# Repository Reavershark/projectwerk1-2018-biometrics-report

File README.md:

# projectwerk1-2018-biometrics-report
Report document of the course "projectwerk 1"

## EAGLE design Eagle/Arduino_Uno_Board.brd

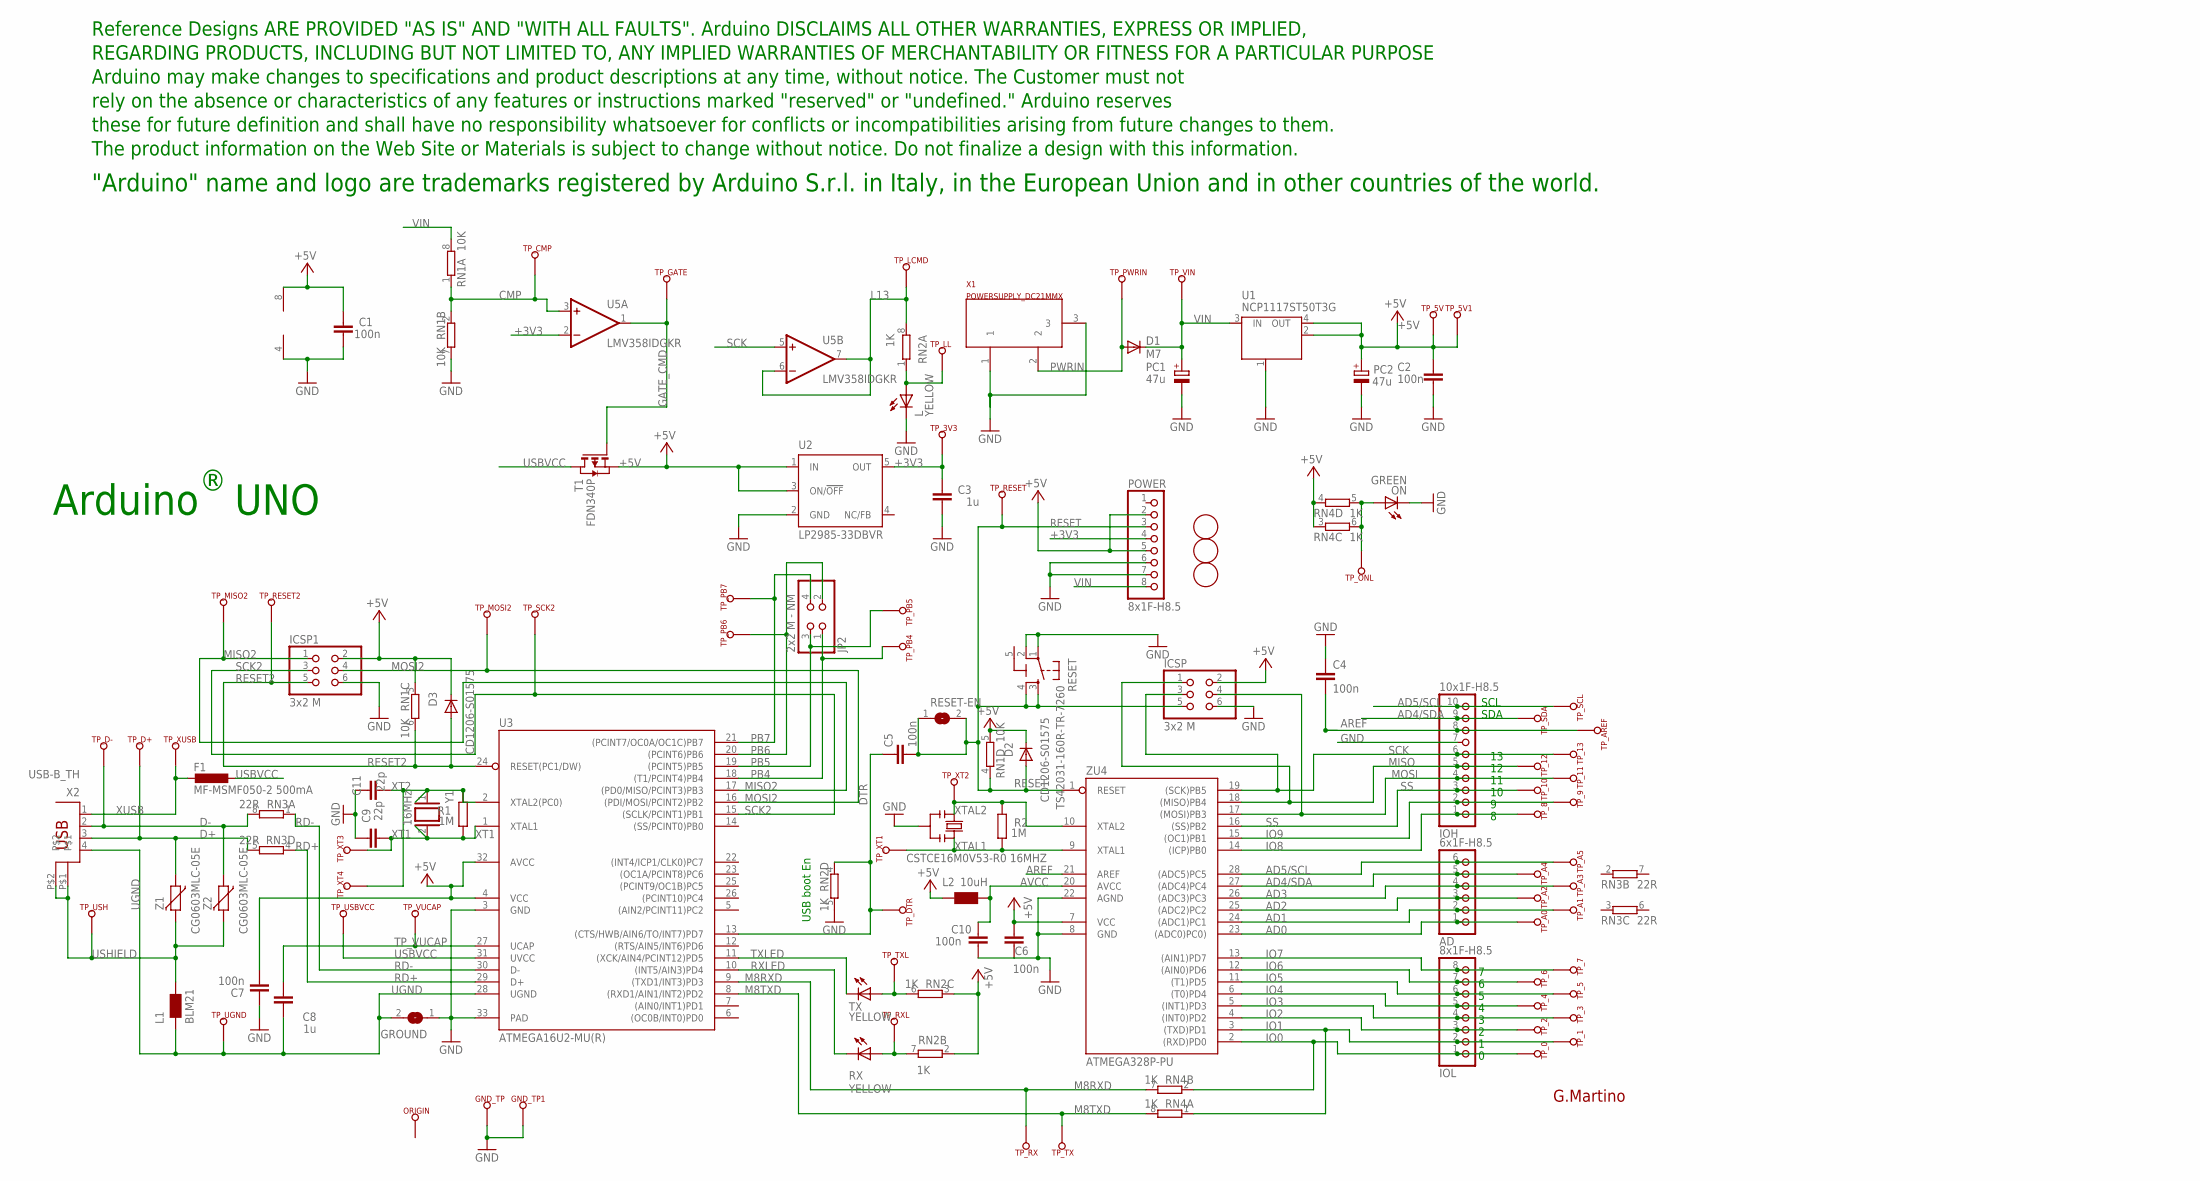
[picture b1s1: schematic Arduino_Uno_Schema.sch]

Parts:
AD: 6x1F-H8.5; 1X06
C1, C2, C4, C5, C6, C7, C10: 100n; C0603-ROUND
C3, C8: 1u; C0603-ROUND
C9, C11: 22p; C0603-ROUND
D1: M7; SMB
D2, D3: CD1206-S01575; MINIMELF
F1: MF-MSMF050-2 500mA; L1812
FD1, FD2, FD3: FIDUCIALMOUNT; FIDUCIA-MOUNT
GND_TP, GND_TP1: TP_SP; TP-SP
GROUND: SJ
ICSP, ICSP1: 3x2 M; 2X03
IOH: 10x1F-H8.5; 1X10
IOL: 8x1F-H8.5; 1X08
JP2: 2x2 M - NM; 2X02
L: YELLOW; CHIP-LED0805
L1: BLM21; 0805
L2: 10uH; 0805
ON: GREEN; CHIP-LED0805
ORIGIN: TP_SP; TP-SP
PC1, PC2: 47u; PANASONIC_D
POWER: 8x1F-H8.5; 1X08
R1, R2: 1M; R0603-ROUND
RESET: TS42031-160R-TR-7260; TS42
RESET-EN: SJ
RN1: 10K; CAY16
RN2, RN4: 1K; CAY16
RN3: 22R; CAY16
RX: YELLOW; CHIP-LED0805
T1: FDN340P; SOT-23
TP_0, TP_1, TP_2, TP_3, TP_3V3, TP_4, TP_5, TP_5V, TP_5V1, TP_6, TP_7, TP_8, TP_9, TP_10, TP_11, TP_12, TP_13: TP_SP; TP-SP
TP_A0, TP_A1, TP_A2, TP_A3, TP_A4, TP_A5: TP_SP; TP-SP
TP_AREF: TP_SP; TP-SP
TP_CMP: TP_SP; TP-SP
TP_D+: TP_SP; TP-SP
TP_D-: TP_SP; TP-SP
TP_DTR: TP_SP; TP-SP
TP_GATE: TP_SP; TP-SP
TP_LCMD: TP_SP; TP-SP
TP_LL: TP_SP; TP-SP
TP_MISO2: TP_SP; TP-SP
TP_MOSI2: TP_SP; TP-SP
TP_ONL: TP_SP; TP-SP
TP_PB4, TP_PB5, TP_PB6, TP_PB7: TP_SP; TP-SP
TP_PWRIN: TP_SP; TP-SP
TP_RESET, TP_RESET2: TP_SP; TP-SP
TP_RX: TP_SP; TP-SP
TP_RXL: TP_SP; TP-SP
TP_SCK2: TP_SP; TP-SP
TP_SCL: TP_SP; TP-SP
TP_SDA: TP_SP; TP-SP
TP_TX: TP_SP; TP-SP
TP_TXL: TP_SP; TP-SP
TP_UGND: TP_SP; TP-SP
TP_USBVCC: TP_SP; TP-SP
TP_USH: TP_SP; TP-SP
TP_VIN: TP_SP; TP-SP
TP_VUCAP: TP_SP; TP-SP
TP_XT1, TP_XT2, TP_XT3, TP_XT4: TP_SP; TP-SP
TP_XUSB: TP_SP; TP-SP
TX: YELLOW; CHIP-LED0805
U1: NCP1117ST50T3G; SOT223
U2: LP2985-33DBVR; SOT23-DBV
U3: ATMEGA16U2-MU(R); MLF32
U5: LMV358IDGKR; MSOP08
U$1: DISCLAIMER
X1: POWERSUPPLY_DC21MMX; POWERSUPPLY_DC-21MM
X2: USB-B_TH; PN61729
Y1: 16MHz; QS
Y2: CSTCE16M0V53-R0 16MHZ; RESONATOR
Z1, Z2: CG0603MLC-05E; CT/CN0603
ZU4: ATMEGA328P-PU; DIL28-3

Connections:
5-GND: RESET.5 (5-GND)
+3V3: C3.2, POWER.4, TP_3V3.X, U2.5 (OUT), U5.2 (-IN)
+5V: C1.2, C2.2, C6.2, C7.1, D2.C, D3.C, ICSP.2, ICSP1.2, L2.1, PC2.+, POWER.2, POWER.5, RN1.3 (1), RN1.5 (2), RN2.2 (1), RN2.3 (1), RN4.3 (1), RN4.4 (1), T1.2 (S), TP_5V.X, TP_5V1.X, U1.2 (OUT), U1.4 (OUT), U2.1 (IN), U2.3 (ON/!OFF), U3.4 (VCC), U3.32 (AVCC), U5.8 (V+), ZU4.7 (VCC)
AD0: AD.1, TP_A0.X, ZU4.23 ((ADC0)PC0))
AD1: AD.2, TP_A1.X, ZU4.24 ((ADC1)PC1)
AD2: AD.3, TP_A2.X, ZU4.25 ((ADC2)PC2)
AD3: AD.4, TP_A3.X, ZU4.26 ((ADC3)PC3)
AD4/SDA: AD.5, IOH.9, TP_A4.X, TP_SDA.X, ZU4.27 ((ADC4)PC4)
AD5/SCL: AD.6, IOH.10, TP_A5.X, TP_SCL.X, ZU4.28 ((ADC5)PC5)
AREF: C4.2, IOH.8, TP_AREF.X, ZU4.21 (AREF)
AVCC: C10.2, L2.2, ZU4.20 (AVCC)
CMP: RN1.1, RN1.2 (1), TP_CMP.X, U5.3 (+IN)
D+: RN3.5 (2), TP_D+.X, X2.3, Z1.1
D-: RN3.8 (2), TP_D-.X, X2.2, Z2.1
DTR: C5.1, RN2.4 (1), TP_DTR.X, U3.13 ((CTS/HWB/AIN6/TO/INT7)PD7)
GATE_CMD: T1.3 (G), TP_GATE.X, U5.1 (OUT)
GND: C1.1, C2.1, C3.1, C4.1, C6.1, C7.2, C9.2, C10.1, C11.2, GND_TP.X, GND_TP1.X, GROUND.1, ICSP.6, ICSP1.6, IOH.7, L.C, ON.C, PC1.-, PC2.-, POWER.6, POWER.7, RESET.1, RESET.2, RN1.7 (2), RN2.5 (2), U1.1 (GND/ADJ), U2.2 (GND), U3.3 (GND), U3.33 (PAD), U5.4 (V-), X1.1, X1.3, Y2.2, ZU4.8 (GND), ZU4.22 (AGND)
IO0: IOL.1, RN4.2 (1), TP_0.X, ZU4.2 ((RXD)PD0)
IO1: IOL.2, RN4.1, TP_1.X, ZU4.3 ((TXD)PD1)
IO2: IOL.3, TP_2.X, ZU4.4 ((INT0)PD2)
IO3: IOL.4, TP_3.X, ZU4.5 ((INT1)PD3)
IO4: IOL.5, TP_4.X, ZU4.6 ((T0)PD4)
IO5: IOL.6, TP_5.X, ZU4.11 ((T1)PD5)
IO6: IOL.7, TP_6.X, ZU4.12 ((AIN0)PD6)
IO7: IOL.8, TP_7.X, ZU4.13 ((AIN1)PD7)
IO8: IOH.1, TP_8.X, ZU4.14 ((ICP)PB0)
IO9: IOH.2, TP_9.X, ZU4.15 ((OC1)PB1)
L13: RN2.8 (2), TP_LCMD.X, U5.6 (-IN), U5.7 (OUT)
M8RXD: RN4.7 (2), TP_RX.X, U3.9 ((TXD1/INT3)PD3)
M8TXD: RN4.8 (2), TP_TX.X, U3.8 ((RXD1/AIN1/INT2)PD2)
MISO: ICSP.1, IOH.5, TP_12.X, ZU4.18 ((MISO)PB4)
MISO2: ICSP1.1, TP_MISO2.X, U3.17 ((PD0/MISO/PCINT3)PB3)
MOSI: ICSP.4, IOH.4, TP_11.X, ZU4.17 ((MOSI)PB3)
MOSI2: ICSP1.4, TP_MOSI2.X, U3.16 ((PDI/MOSI/PCINT2)PB2)
unnamed: L.A, RN2.1, TP_LL.X
unnamed: ON.A, RN4.5 (2), RN4.6 (2), TP_ONL.X
unnamed: RN2.7 (2), RX.A, TP_RXL.X
unnamed: RN2.6 (2), TP_TXL.X, TX.A
PB4: JP2.1, TP_PB4.X, U3.18 ((T1/PCINT4)PB4)
PB5: JP2.3, TP_PB5.X, U3.19 ((PCINT5)PB5)
PB6: JP2.2, TP_PB6.X, U3.20 ((PCINT6)PB6)
PB7: JP2.4, TP_PB7.X, U3.21 ((PCINT7/OC0A/OC1C)PB7)
PWRIN: D1.A, TP_PWRIN.X, X1.2
RD+: RN3.4 (1), U3.29 (D+)
RD-: RN3.1, U3.30 (D-)
RESET: C5.2, D2.A, ICSP.5, POWER.3, RESET.3, RESET.4, RESET-EN.1, RESET-EN.2, RN1.4 (1), TP_RESET.X, ZU4.1 (RESET)
RESET2: D3.A, ICSP1.5, RN1.6 (2), TP_RESET2.X, U3.24 (RESET(PC1/DW))
RXLED: RX.C, U3.10 ((INT5/AIN3)PD4)
SCK: ICSP.3, IOH.6, TP_13.X, U5.5 (+IN), ZU4.19 ((SCK)PB5)
SCK2: ICSP1.3, TP_SCK2.X, U3.15 ((SCLK/PCINT1)PB1)
SS: IOH.3, TP_10.X, ZU4.16 ((SS)PB2)
TP_VUCAP: C8.1, TP_VUCAP.X, U3.27 (UCAP)
TXLED: TX.C, U3.11 ((XCK/AIN4/PCINT12)PD5)
UGND: C8.2, GROUND.2, L1.1, TP_UGND.X, U3.28 (UGND), X2.4
USBVCC: F1.1, T1.1 (D), TP_USBVCC.X, U3.31 (UVCC)
USHIELD: L1.2, TP_USH.X, X2.P$1, X2.P$2, Z1.2, Z2.2
VIN: D1.C, PC1.+, POWER.8, RN1.8 (2), TP_VIN.X, U1.3 (IN)
XT1: C9.1, R1.1, TP_XT3.X, U3.1 (XTAL1), Y1.2
XT2: C11.1, R1.2, TP_XT4.X, U3.2 (XTAL2(PC0)), Y1.1
XTAL1: R2.1, TP_XT1.X, Y2.3, ZU4.9 (XTAL1)
XTAL2: R2.2, TP_XT2.X, Y2.1, ZU4.10 (XTAL2)
XUSB: F1.2, TP_XUSB.X, X2.1

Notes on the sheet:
Arduino UNO
USB boot En
SDA
SCL
G.Martino

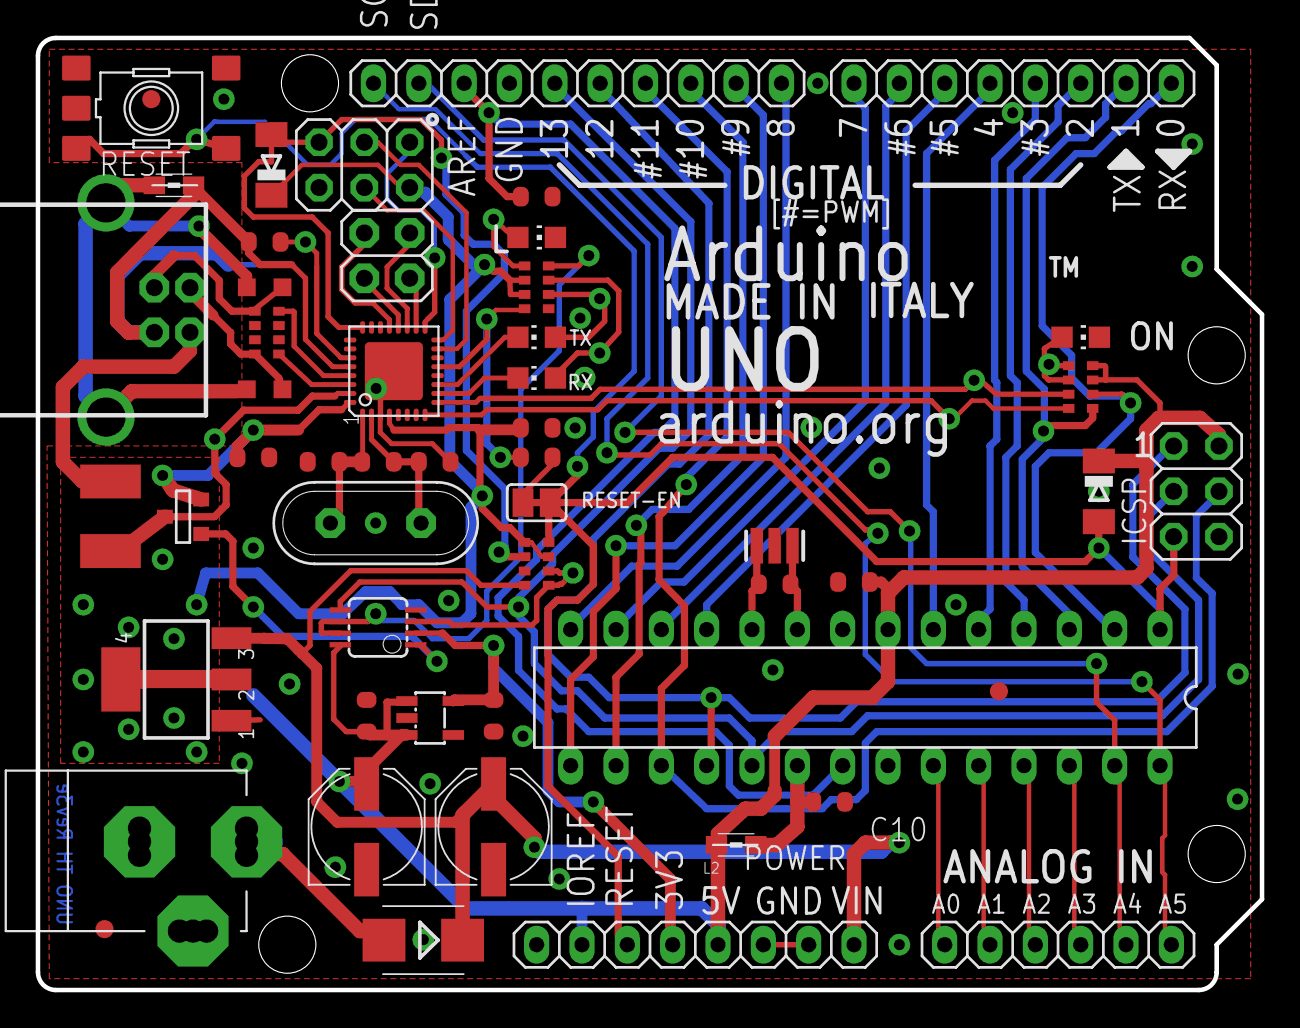
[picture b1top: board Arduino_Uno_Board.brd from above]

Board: 2 copper layers, 68.6 x 53.3 mm, 116 parts (1 on the bottom side), 61 nets.

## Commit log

2018-03-15 Update .gitignore with vim swap files
2018-03-15 Empty LaTeX file
2018-03-15 Added link to compiled pdf
2018-03-15 Added .gitignore for pdf files
2018-03-15 MarkDown formatting
2018-03-15 English
2018-03-15 Added section outlines and some blind text
2018-03-15 Better chapter format
2018-03-17 Update URL
2018-03-19 Cleanup
2018-03-19 Updated copyright notice
2018-03-20 Example syntax
2018-05-04 Contact
2018-05-10 Task assignment
2018-05-11 Heb bepaalde dingen ingevuld, Waar niets staat is te vaag voor me (sorry)
2018-05-12 Formatted hardware
2018-05-12 Updated link
2018-05-16 Example reference
2018-05-16 Block diagram
2018-05-16 Links toegevoegd, nog niet alle links staan er op
2018-05-16 Begin serial protocol
2018-05-16 Protocols
2018-05-16 Alle links zijn toegevoegd
2018-05-16 De uitleg van de arduino toegevoegd
2018-05-17 Bibliografie
2018-05-17 Description, formatting
2018-05-17 Removed Eagle files
2018-05-17 Java daemon
2018-05-17 Uitleg code toegevoegd (PS voor de zekerheid best eens kijken of alles juist is wat ik zeg)
2018-05-17 Schema toegevoegd
2018-05-17 Formatting arduino
2018-05-18 Started gui
2018-05-18 citaties toegevoegd aan text
2018-05-18 Javafx
2018-05-18 Tasks
2018-05-18 Besluit
2018-05-18 Linebreaks
2018-05-18 video arduino toegevoegd
2018-05-18 Videos
2018-05-18 Removed audio
2018-05-18 voorblad toegevoegd
2018-05-18 Added pdf's
2018-05-18 Removed link
2018-05-18 Typo
2018-05-18 Rename
